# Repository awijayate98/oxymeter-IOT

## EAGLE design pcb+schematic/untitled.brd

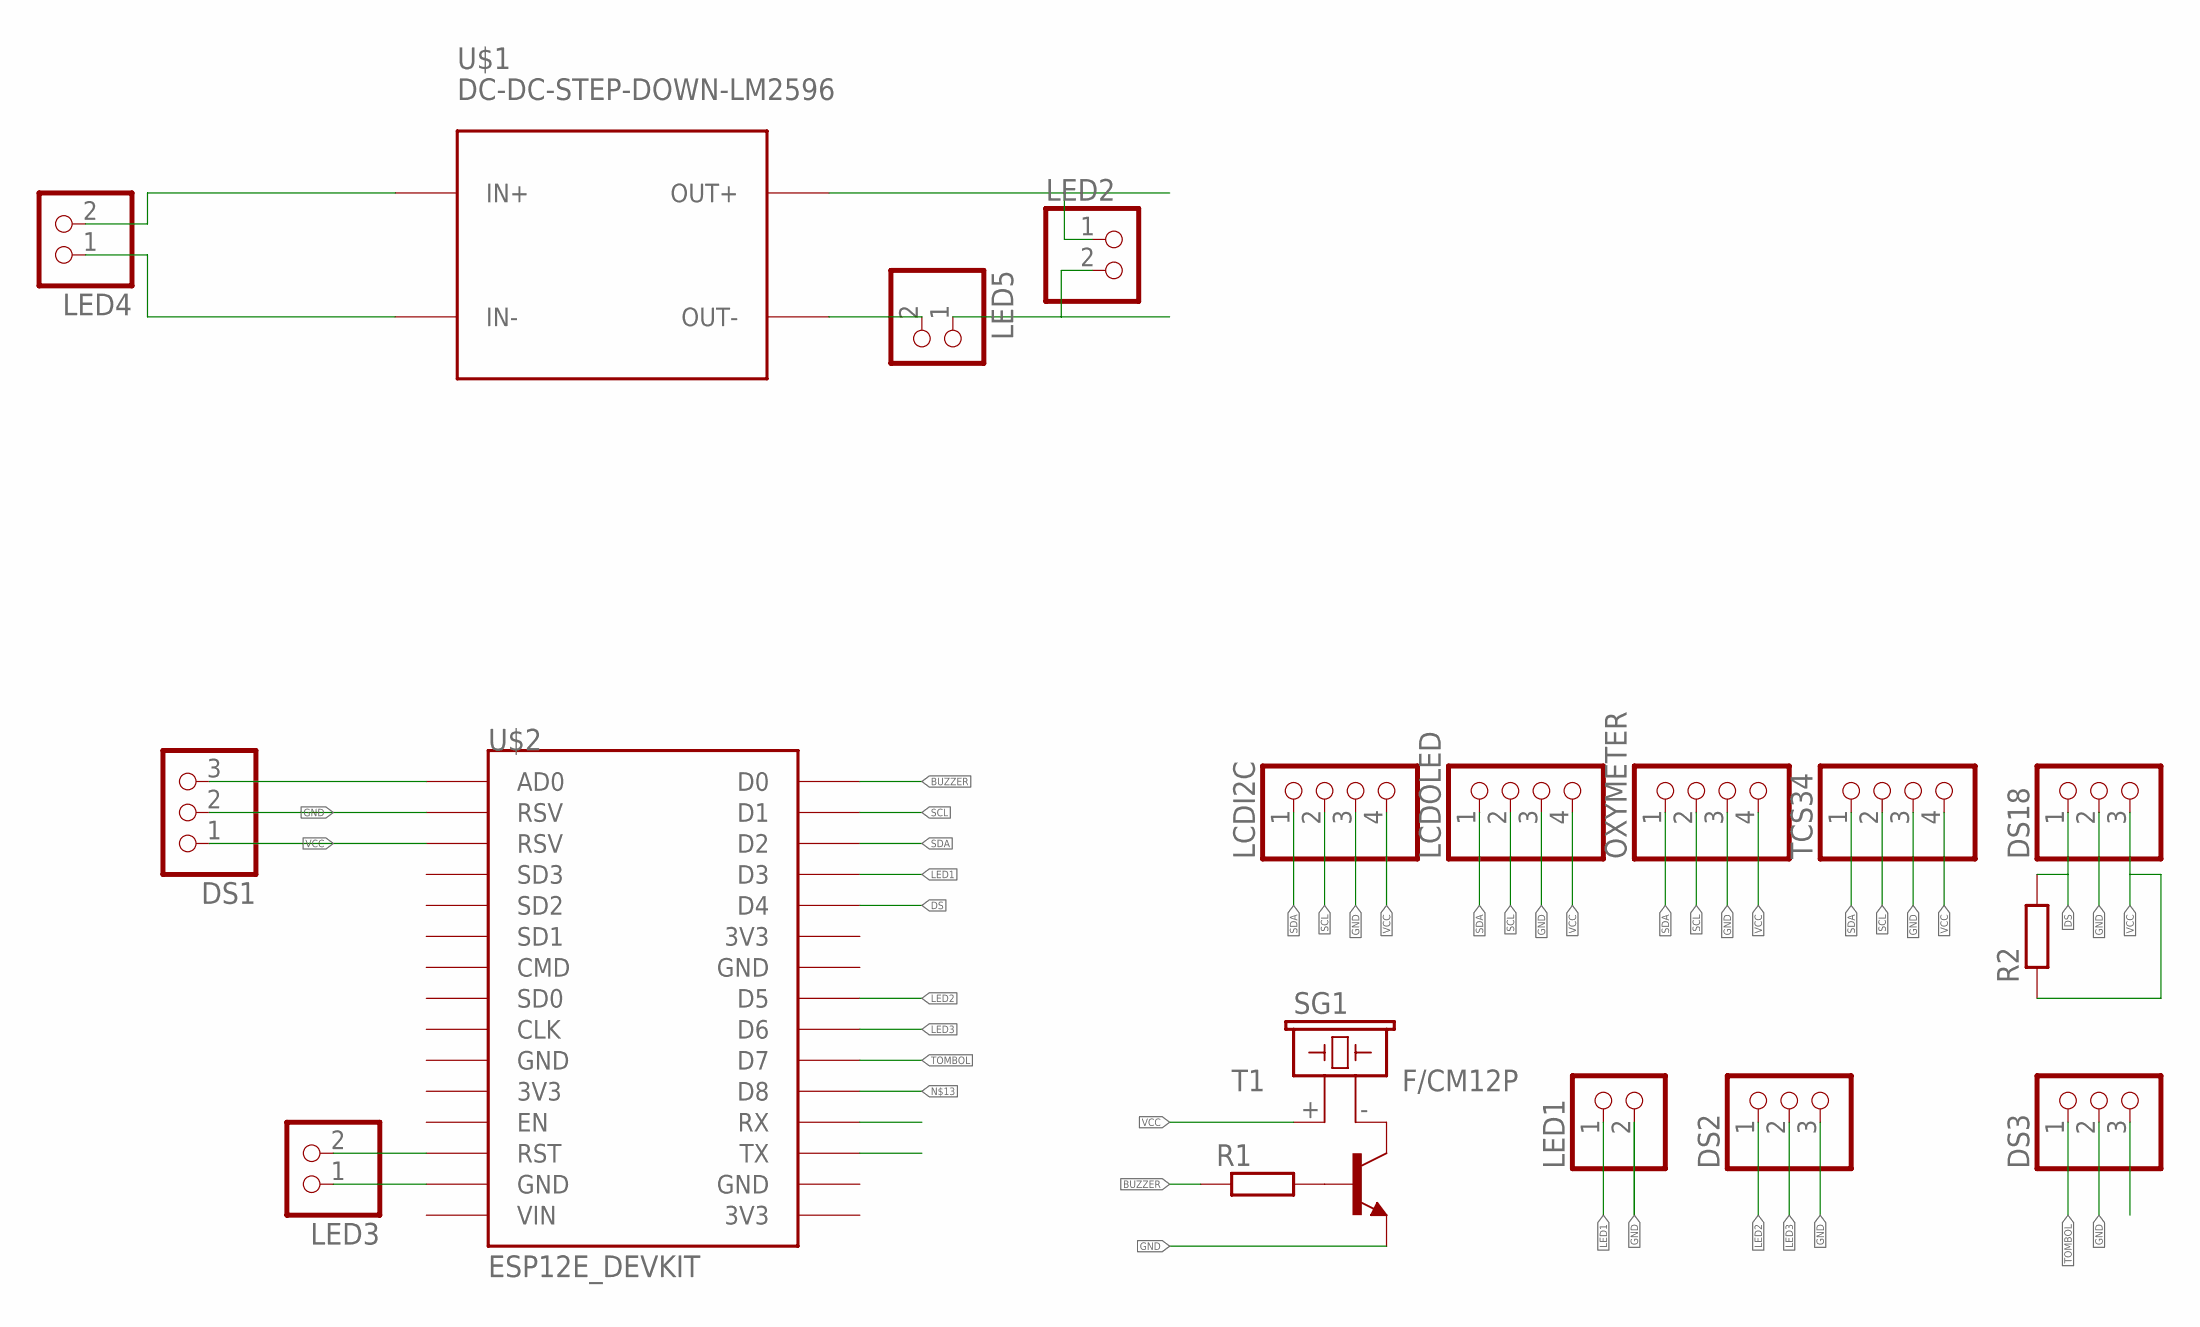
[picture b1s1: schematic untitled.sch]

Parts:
DS1, DS2, DS3, DS18: PINHD-1X3; 1X03
LCDI2C: PINHD-1X4; 1X04
LCDOLED: PINHD-1X4; 1X04
LED1, LED2, LED3, LED4, LED5: PINHD-1X2; 1X02
OXYMETER: PINHD-1X4; 1X04
R1, R2: R-EU_0207/10; 0207/10
SG1: F/CM12P
T1: -NPN-TO92; TO92
TCS34: PINHD-1X4; 1X04
U$1: DC-DC-STEP-DOWN-LM2596
U$2: ESP12E_DEVKIT

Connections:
BUZZER: R1.1, U$2.D0
DS: DS18.1, R2.2, U$2.D4
GND: DS1.2, DS2.3, DS3.2, DS18.2, LCDI2C.3, LCDOLED.3, LED1.2, LED2.2, LED5.1, OXYMETER.3, T1.1 (E), TCS34.3, U$2.RSV@0 (RSV)
LED1: LED1.1, U$2.D3
LED2: DS2.1, U$2.D5
LED3: DS2.2, U$2.D6
unnamed: LED3.2, U$2.RST
unnamed: SG1.- (2), T1.3 (C)
unnamed: R1.2, T1.2 (B)
unnamed: LED4.2, U$1.IN+
unnamed: LED4.1, U$1.IN-
unnamed: LED5.2, U$1.OUT-
unnamed: LED3.1, U$2.GND@1 (GND)
unnamed: DS1.3, U$2.AD0
SCL: LCDI2C.2, LCDOLED.2, OXYMETER.2, TCS34.2, U$2.D1
SDA: LCDI2C.1, LCDOLED.1, OXYMETER.1, TCS34.1, U$2.D2
TOMBOL: DS3.1, U$2.D7
VCC: DS1.1, DS3.3, DS18.3, LCDI2C.4, LCDOLED.4, LED2.1, OXYMETER.4, R2.1, SG1.+ (1), TCS34.4, U$1.OUT+, U$2.RSV@1 (RSV)

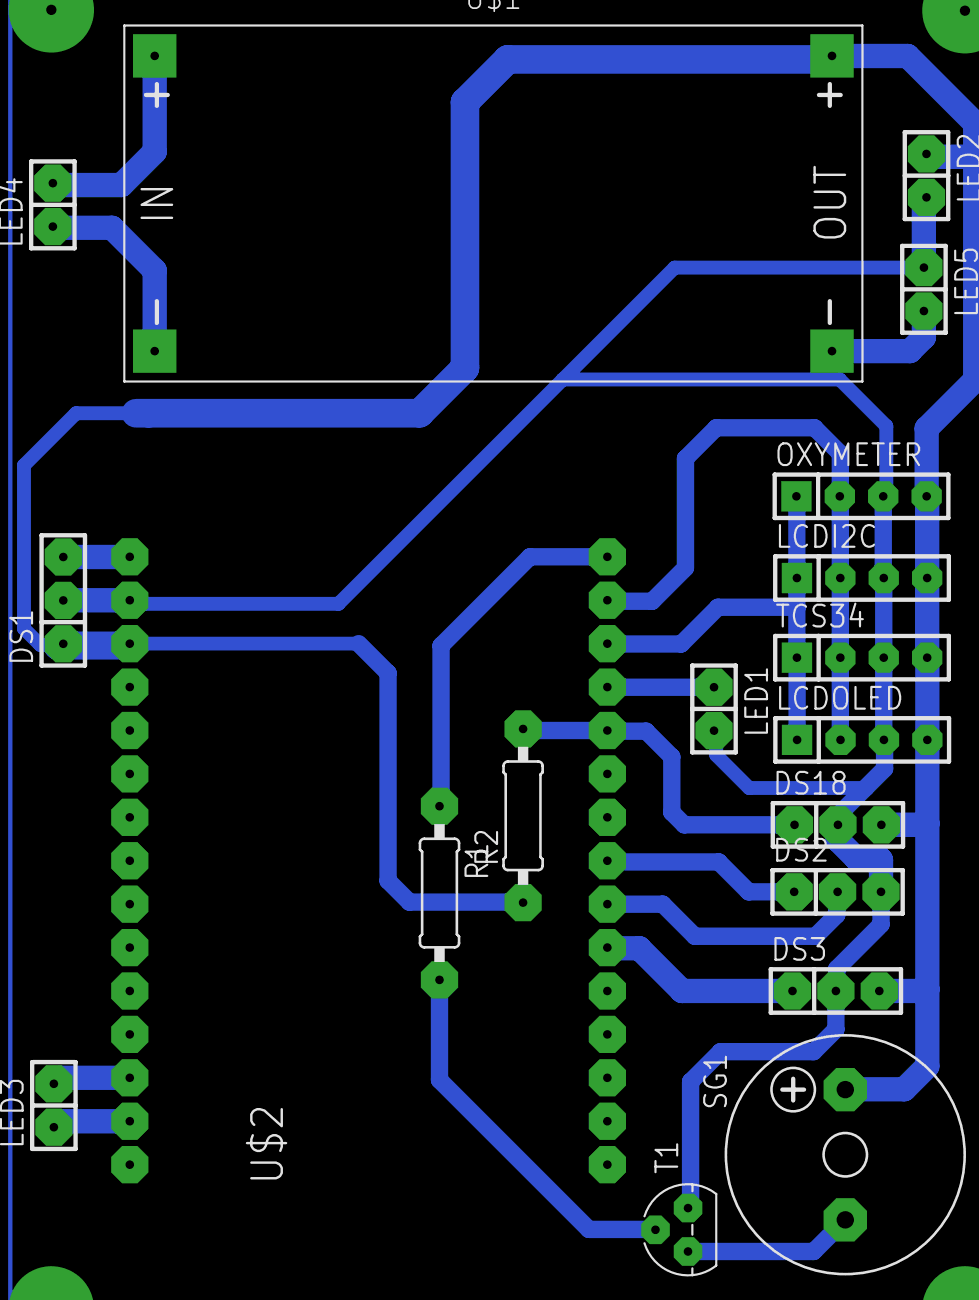
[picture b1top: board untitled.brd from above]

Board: 2 copper layers, 19 parts (0 on the bottom side), 18 nets.

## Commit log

2025-08-18 baca.txt
2025-08-19 update.sh

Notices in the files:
parts and their libraries:
diy-modules: Released under the Creative Commons Attribution 4.0 International License: http://creativecommons.org/licenses/by/4.0
